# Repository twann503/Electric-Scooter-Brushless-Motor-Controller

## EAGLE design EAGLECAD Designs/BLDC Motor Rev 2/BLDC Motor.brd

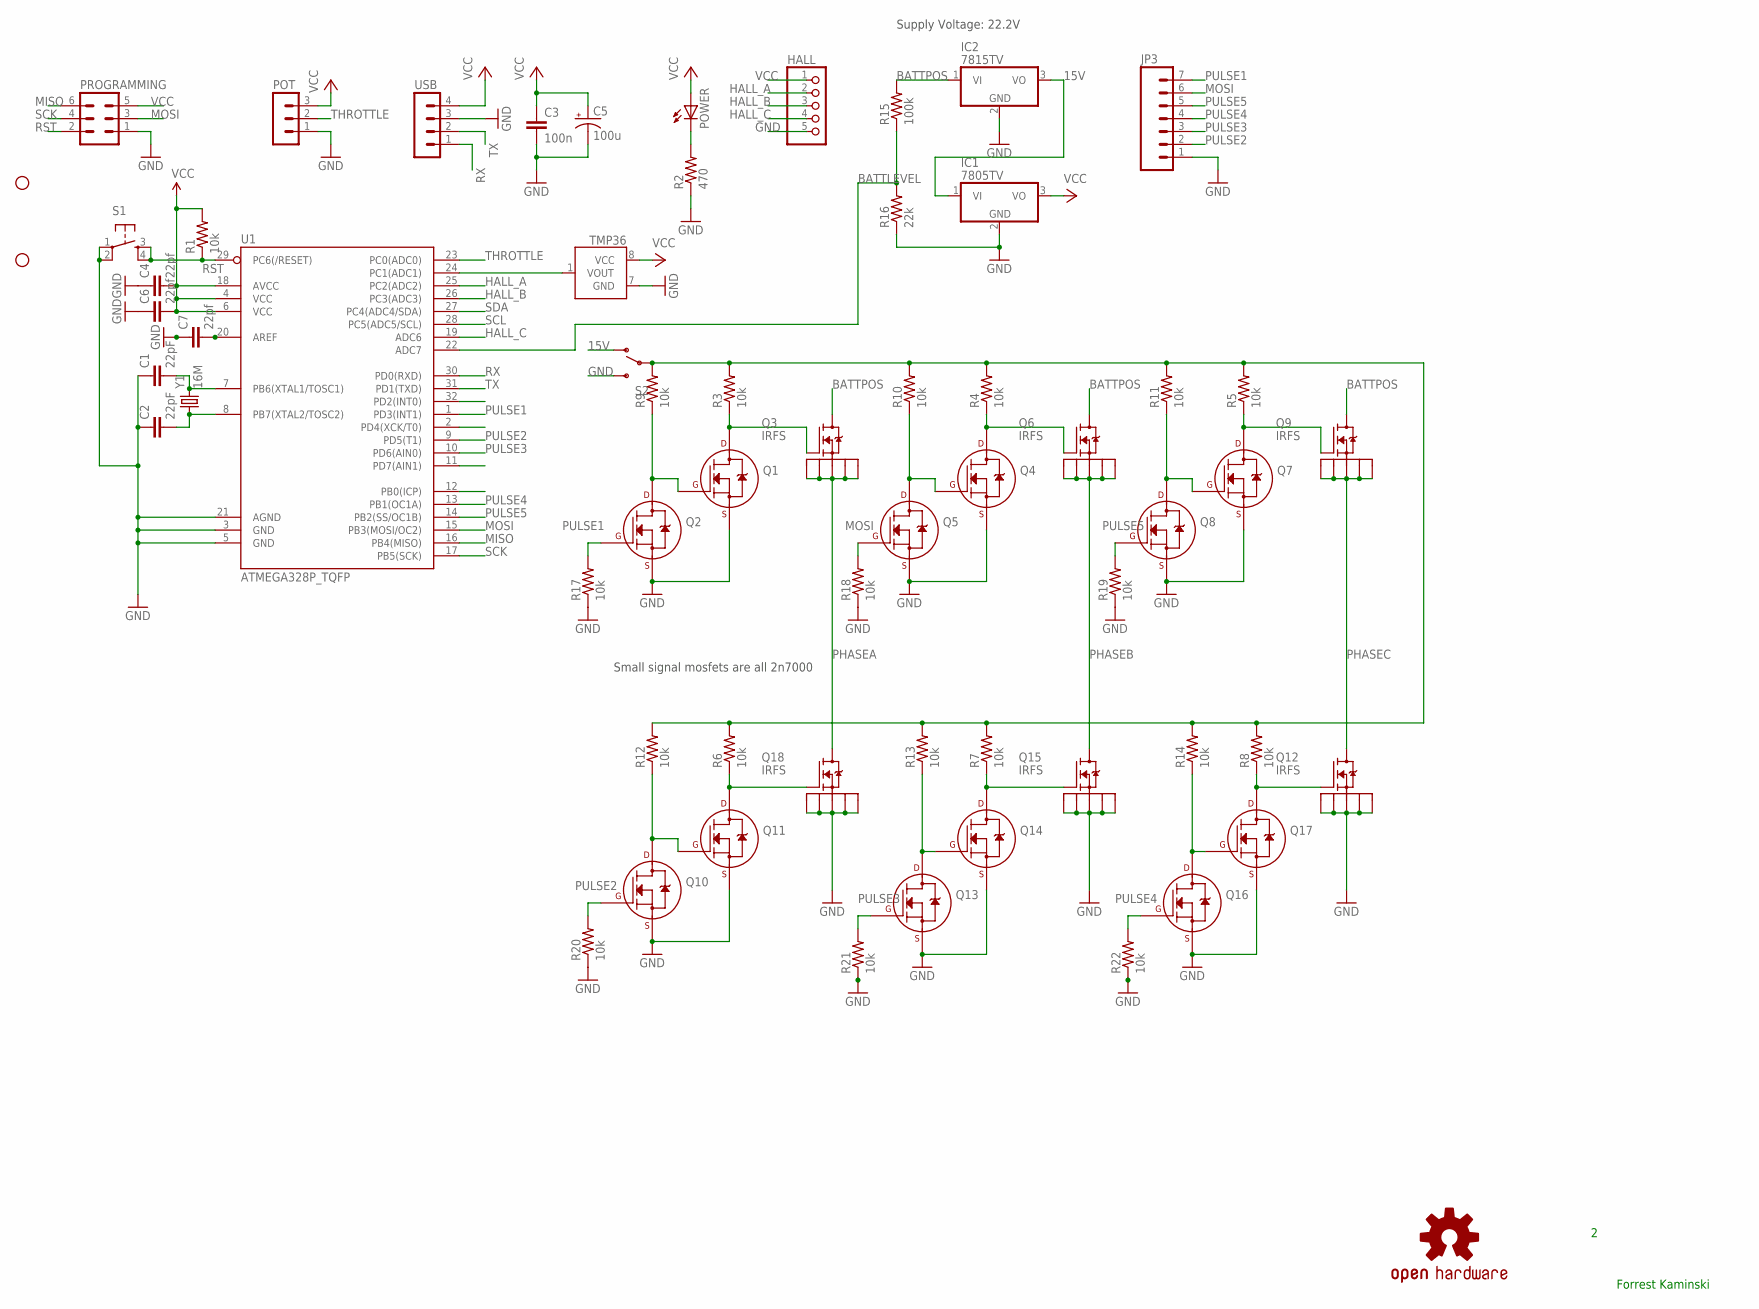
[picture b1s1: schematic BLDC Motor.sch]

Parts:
C1, C2: 22pF; 0805
C3: 100n; 0805
C4, C6, C7: 22pf; 0805
C5: 100u; CPOL-RADIAL-100UF-25V
HALL: PINHD-1X5; 1X05
IC1: 7805TV; TO220V
IC2: 7815TV; TO220V
JP1, JP2: STAND-OFF
JP3: M07; 1X07
POT: MA03-1
POWER: LEDSML0805; SML0805
PROGRAMMING: MA03-2
Q1, Q2, Q4, Q5, Q7, Q8, Q10, Q11, Q13, Q14, Q16, Q17: 2N7000_TO92; TO-92
Q3, Q6, Q9, Q12, Q15, Q18: IRFS; D2PAK-7
R1, R3, R4, R5, R6, R7, R8, R9, R10, R11, R12, R13, R14, R17, R18, R19, R20, R21, R22: 10k; 0805
R2: 470; 0805
R15: 100k; 0805
R16: 22k; 0805
S1: TAC_SWITCHPTH; TACTILE-PTH
S2: SWITCH-SPSTPTH_LOCK; SWITCH-SPDT_LOCK.007S
TMP36: TMP36SOIC; SOIC8
U1: ATMEGA328P_TQFP; TQFP32-08
U$1: OSHW-LOGOS; OSHW-LOGO-S
USB: MA04-1
Y1: 16M; HC49US

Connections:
15V: IC1.1 (VI), IC2.3 (VO), S2.1 (O)
BATTLEVEL: R15.1, R16.2, U1.22 (ADC7)
BATTPOS: IC2.1 (VI), Q3.D, Q6.D, Q9.D, R15.2
GND: C1.1, C2.1, C3.2, C4.1, C5.2 (-), C6.1, C7.1, HALL.5, IC1.2 (GND), IC2.2 (GND), JP3.1, POT.1, PROGRAMMING.1, Q1.1 (S), Q2.1 (S), Q4.1 (S), Q5.1 (S), Q7.1 (S), Q8.1 (S), Q10.1 (S), Q11.1 (S), Q12.S1, Q12.S2, Q12.S3, Q12.S4, Q12.S5, Q13.1 (S), Q14.1 (S), Q15.S1, Q15.S2, Q15.S3, Q15.S4, Q15.S5, Q16.1 (S), Q17.1 (S), Q18.S1, Q18.S2, Q18.S3, Q18.S4, Q18.S5, R2.1, R16.1, R17.1, R18.1, R19.1, R20.1, R21.1, R22.1, S1.1, S1.2, S2.3 (S), TMP36.7 (GND), U1.3 (GND), U1.5 (GND), U1.21 (AGND), USB.3
HALL_A: HALL.2, U1.25 (PC2(ADC2))
HALL_B: HALL.3, U1.26 (PC3(ADC3))
HALL_C: HALL.4, U1.19 (ADC6)
MISO: PROGRAMMING.6, U1.16 (PB4(MISO))
MOSI: JP3.6, PROGRAMMING.3, Q5.2 (G), R18.2, U1.15 (PB3(MOSI/OC2))
unnamed: C2.2, U1.8 (PB7(XTAL2/TOSC2)), Y1.1
unnamed: C1.2, U1.7 (PB6(XTAL1/TOSC1)), Y1.2
unnamed: POWER.C, R2.2
unnamed: Q10.3 (D), Q11.2 (G), R12.1
unnamed: Q1.3 (D), Q3.G, R3.1
unnamed: TMP36.1 (VOUT), U1.24 (PC1(ADC1))
unnamed: C7.2, U1.20 (AREF)
unnamed: Q1.2 (G), Q2.3 (D), R9.1
unnamed: Q4.3 (D), Q6.G, R4.1
unnamed: Q4.2 (G), Q5.3 (D), R10.1
unnamed: R3.2, R4.2, R5.2, R6.2, R7.2, R8.2, R9.2, R10.2, R11.2, R12.2, R13.2, R14.2, S2.2
unnamed: Q7.3 (D), Q9.G, R5.1
unnamed: Q7.2 (G), Q8.3 (D), R11.1
unnamed: Q11.3 (D), Q18.G, R6.1
unnamed: Q13.3 (D), Q14.2 (G), R13.1
unnamed: Q12.G, Q17.3 (D), R8.1
unnamed: Q16.3 (D), Q17.2 (G), R14.1
unnamed: Q14.3 (D), Q15.G, R7.1
PHASEA: Q3.S1, Q3.S2, Q3.S3, Q3.S4, Q3.S5, Q18.D
PHASEB: Q6.S1, Q6.S2, Q6.S3, Q6.S4, Q6.S5, Q15.D
PHASEC: Q9.S1, Q9.S2, Q9.S3, Q9.S4, Q9.S5, Q12.D
PULSE1: JP3.7, Q2.2 (G), R17.2, U1.1 (PD3(INT1))
PULSE2: JP3.2, Q10.2 (G), R20.2, U1.9 (PD5(T1))
PULSE3: JP3.3, Q13.2 (G), R21.2, U1.10 (PD6(AIN0))
PULSE4: JP3.4, Q16.2 (G), R22.2, U1.13 (PB1(OC1A))
PULSE5: JP3.5, Q8.2 (G), R19.2, U1.14 (PB2(SS/OC1B))
RST: PROGRAMMING.2, R1.1, S1.3, S1.4, U1.29 (PC6(/RESET))
RX: U1.30 (PD0(RXD)), USB.1
SCK: PROGRAMMING.4, U1.17 (PB5(SCK))
SCL: U1.28 (PC5(ADC5/SCL))
SDA: U1.27 (PC4(ADC4/SDA))
THROTTLE: POT.2, U1.23 (PC0(ADC0))
TX: U1.31 (PD1(TXD)), USB.2
VCC: C3.1, C4.2, C5.1 (+), C6.2, HALL.1, IC1.3 (VO), POT.3, POWER.A, PROGRAMMING.5, R1.2, TMP36.8 (VCC), U1.4 (VCC), U1.6 (VCC), U1.18 (AVCC), USB.4

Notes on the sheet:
Supply Voltage: 22.2V
Forrest Kaminski
Small signal mosfets are all 2n7000

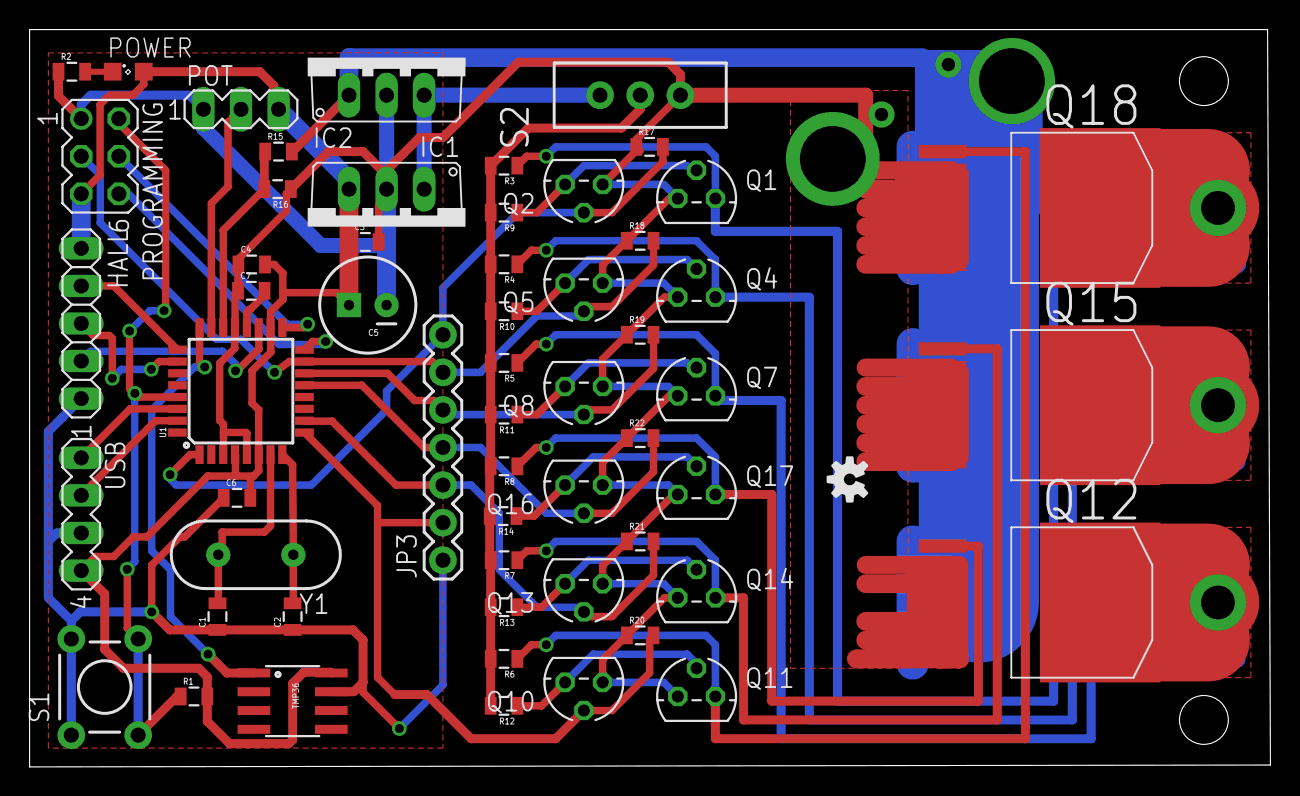
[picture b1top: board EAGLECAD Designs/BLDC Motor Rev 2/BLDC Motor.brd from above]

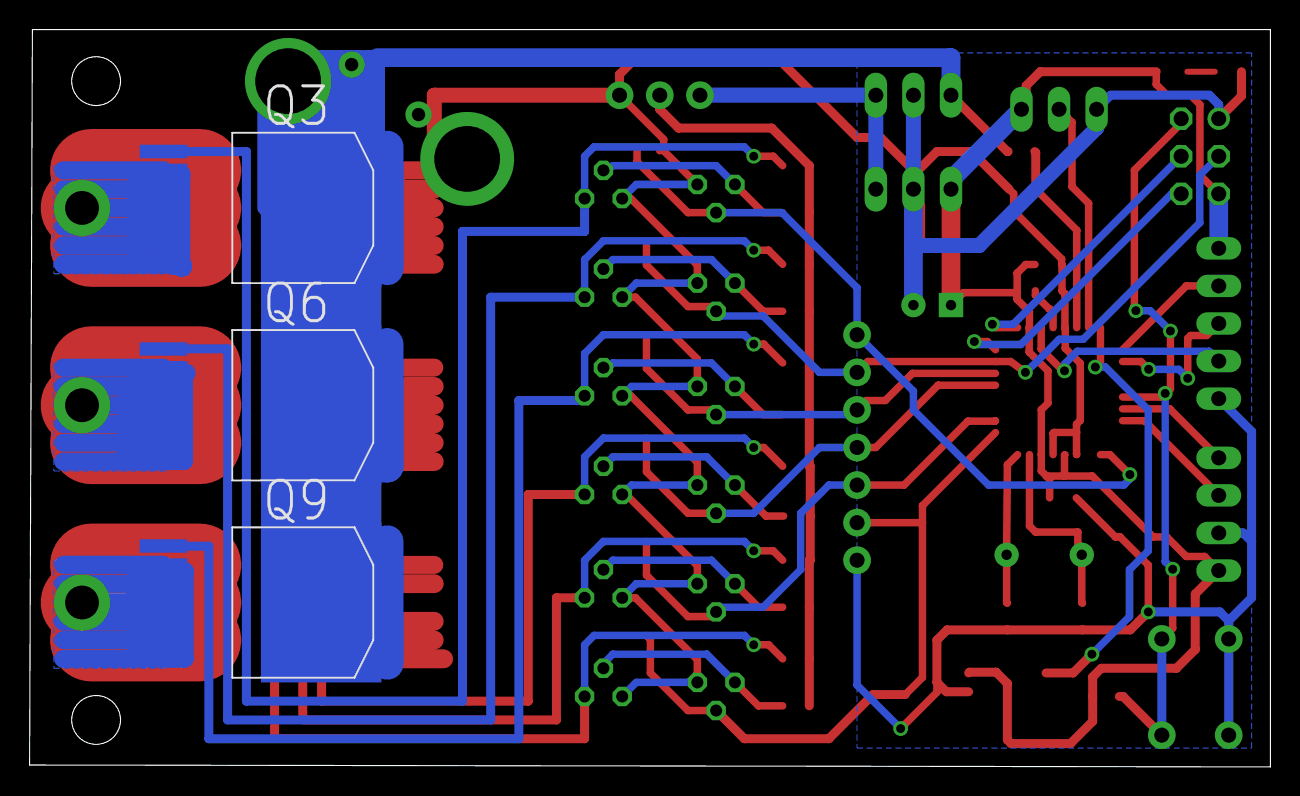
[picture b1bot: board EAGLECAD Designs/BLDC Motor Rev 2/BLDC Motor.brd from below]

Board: 2 copper layers, 83.9 x 49.8 mm, 63 parts (3 on the bottom side), 41 nets.

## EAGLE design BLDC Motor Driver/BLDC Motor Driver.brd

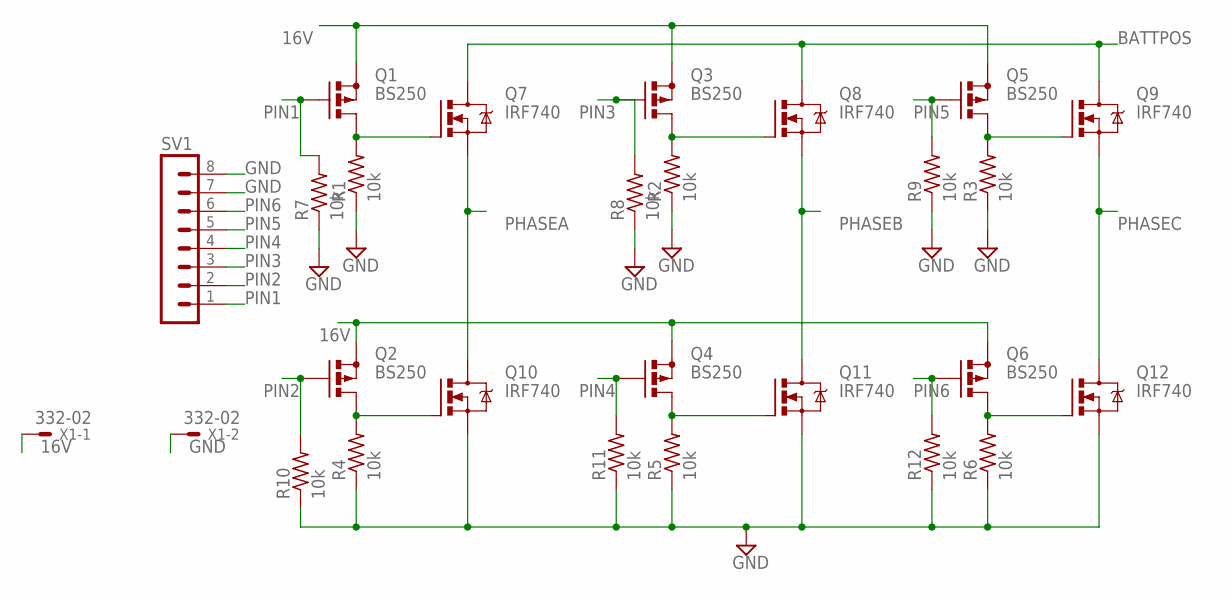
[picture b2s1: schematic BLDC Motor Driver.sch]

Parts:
Q1, Q2, Q3, Q4, Q5, Q6: BS250; SOT54E
Q7, Q8, Q9, Q10, Q11, Q12: IRF740; TO220BV
R1, R2, R3, R4, R5, R6, R7, R8, R9, R10, R11, R12: 10k; R0805
SV1: MA08-1
X1: 332-02

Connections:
16V: Q1.S, Q2.S, Q3.S, Q4.S, Q5.S, Q6.S, X1.1; also elsewhere on the board
BATTPOS: Q7.D, Q8.D, Q9.D
GND: Q10.S, Q11.S, Q12.S, R1.1, R2.1, R3.1, R4.1, R5.1, R6.1, R7.1, R8.1, R9.1, R10.1, R11.1, R12.1, SV1.7, SV1.8, X1.2; also elsewhere on the board
unnamed: Q1.D, Q7.G, R1.2
unnamed: Q3.D, Q8.G, R2.2
unnamed: Q5.D, Q9.G, R3.2
unnamed: Q2.D, Q10.G, R4.2
unnamed: Q4.D, Q11.G, R5.2
unnamed: Q6.D, Q12.G, R6.2
PHASEA: Q7.S, Q10.D
PHASEB: Q8.S, Q11.D
PHASEC: Q9.S, Q12.D
PIN1: Q1.G, R7.2, SV1.1
PIN2: Q2.G, R10.2, SV1.2
PIN3: Q3.G, R8.2, SV1.3
PIN4: Q4.G, R11.2, SV1.4
PIN5: Q5.G, R9.2, SV1.5
PIN6: Q6.G, R12.2, SV1.6

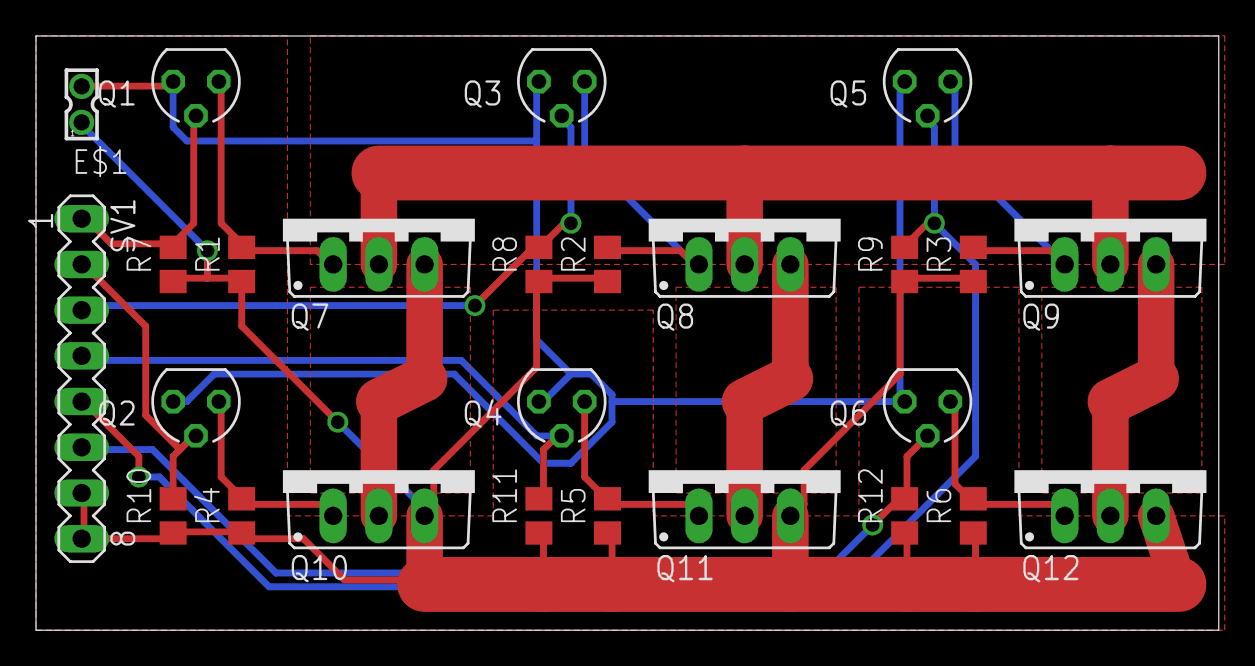
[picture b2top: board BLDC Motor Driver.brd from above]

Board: 2 copper layers, 65.7 x 33.0 mm, 26 parts (0 on the bottom side), 18 nets.

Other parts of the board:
E$1: 332-02

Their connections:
16V: E$1.2; also elsewhere on the board
GND: E$1.1; also elsewhere on the board

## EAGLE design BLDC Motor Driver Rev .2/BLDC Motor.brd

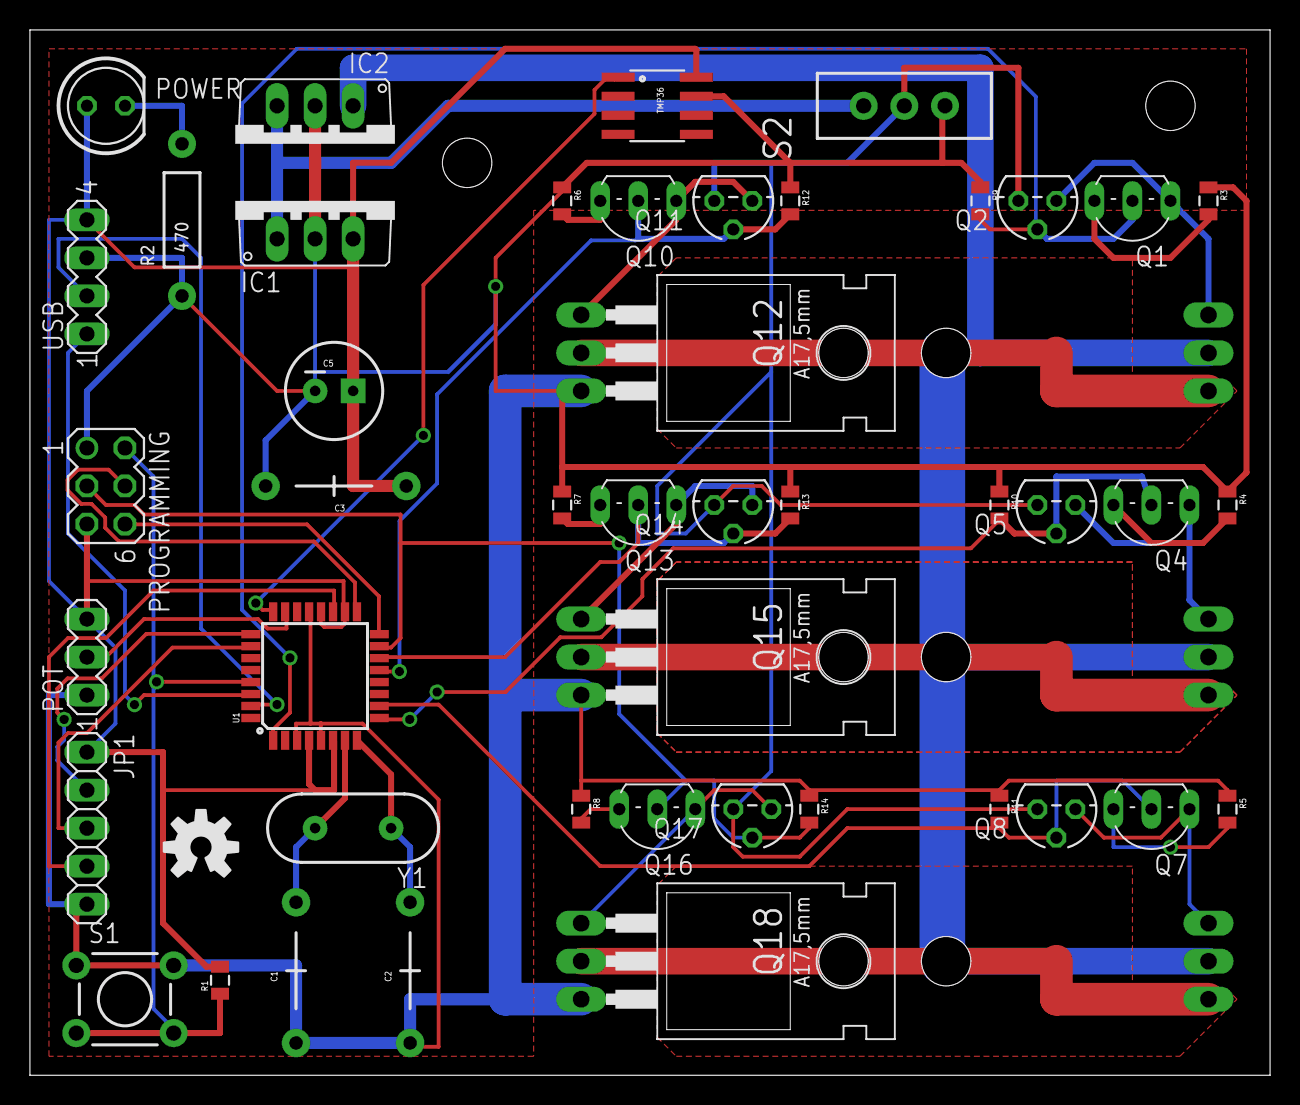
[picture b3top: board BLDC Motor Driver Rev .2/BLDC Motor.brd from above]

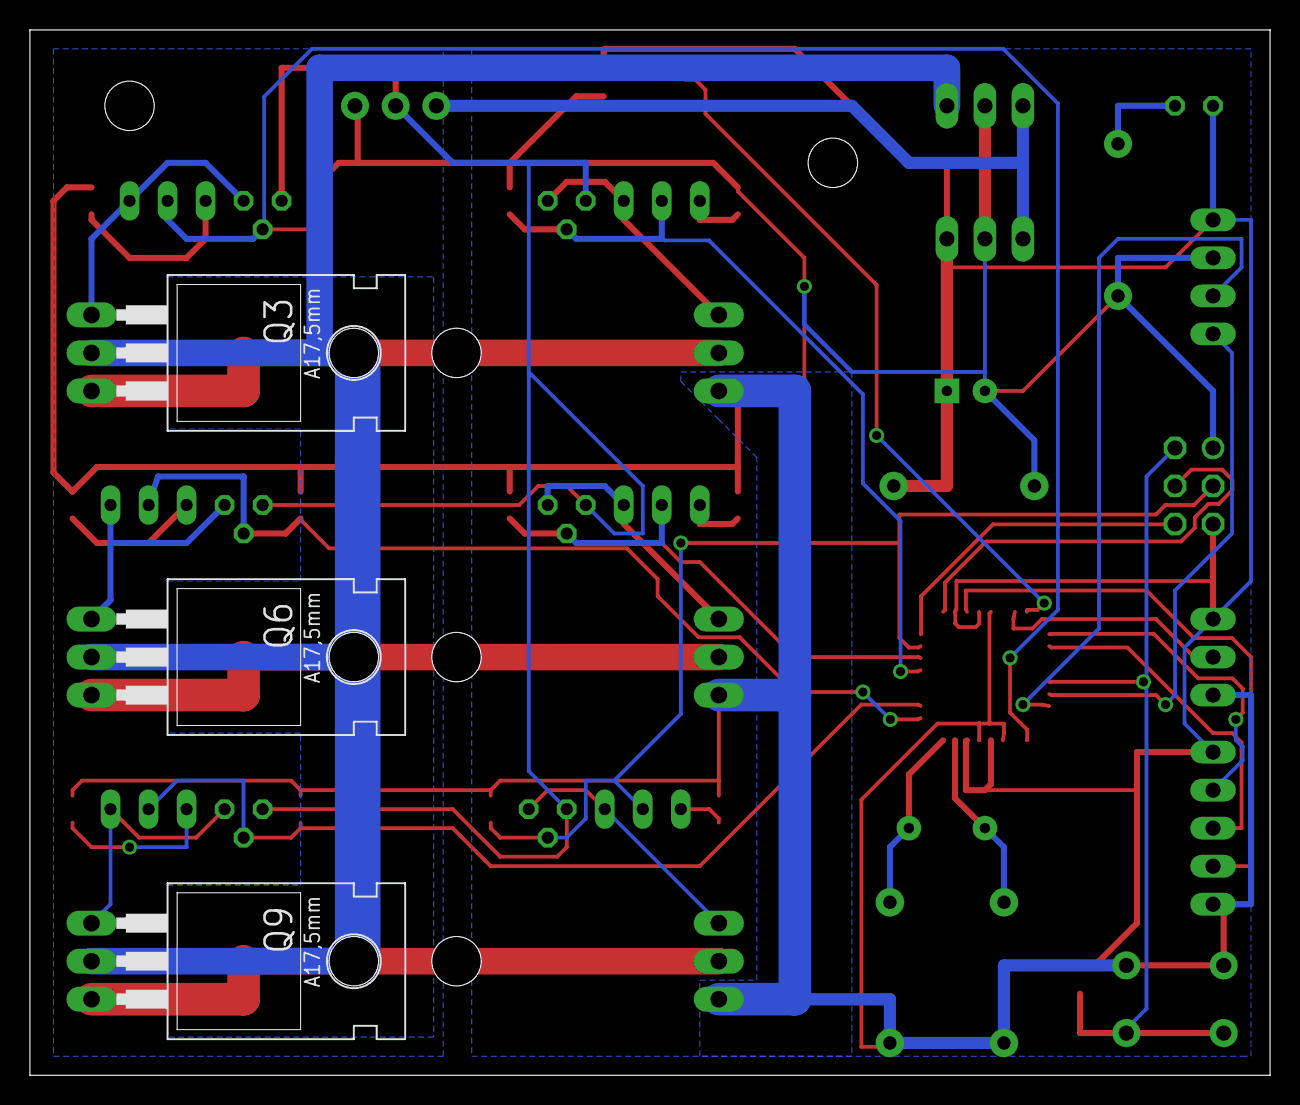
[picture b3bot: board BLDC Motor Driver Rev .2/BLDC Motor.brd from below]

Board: 2 copper layers, 82.9 x 69.8 mm, 51 parts (3 on the bottom side), 39 nets.

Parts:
C1, C2: 22pF; CAP-PTH-LARGE
C3: 0.1u; CAP-PTH-LARGE
C5: 100u; CPOL-RADIAL-100UF-25V
IC1: 7805TV; TO220V
IC2: 7815TV; TO220V
JP1: 1X05
JP2, JP4: STAND-OFF
POT: MA03-1
POWER: LED5MM
PROGRAMMING: MA03-2
Q1, Q4, Q7, Q10, Q13, Q16: TP2104; TO92-OVAL
Q2, Q5, Q8, Q11, Q14, Q17: TO-92
Q3, Q6, Q9, Q12, Q15, Q18: IRFB4115; TO220
R1, R3, R4, R5, R6, R7, R8, R9, R10, R11, R12, R13, R14: 10k; 0805
R2: 470; AXIAL-0.4
S1: TACTILE-PTH
S2: SWITCH-SPDT_LOCK.007S
TMP36: SOIC8
U1: ATMEGA328P_TQFP; TQFP32-08
U$1: OSHW-LOGOM; OSHW-LOGO-M
USB: MA04-1
Y1: 16M; HC49US

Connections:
15V: IC1.1, IC2.3, S2.1
BATTPOS: IC2.1, Q3.2, Q6.2, Q9.2
GND: C1.1, C2.1, C3.2, C5.2, IC1.2, IC2.2, JP1.5, POT.1, PROGRAMMING.1, Q12.3, Q15.3, Q18.3, R2.P$1, R3.1, R4.1, R5.1, R6.1, R7.1, R8.1, R9.1, R10.1, R11.1, R12.1, R13.1, R14.1, S1.1, S1.2, S2.3, TMP36.7, U1.3, U1.5, U1.21, USB.3
HALL_A: JP1.2, U1.25
HALL_B: JP1.3, U1.26
HALL_C: JP1.4, U1.19
MISO: PROGRAMMING.6, U1.16
MOSI: PROGRAMMING.3, Q16.2, Q17.2, R14.2, U1.15
unnamed: C2.2, U1.8, Y1.1
unnamed: C1.2, U1.7, Y1.2
unnamed: POWER.K, R2.P$2
unnamed: Q1.3, R3.2
unnamed: Q1.1, Q2.1, Q3.1
unnamed: TMP36.1, U1.24
unnamed: Q2.3, Q5.3, Q8.3, Q11.3, Q14.3, Q17.3, S2.2
unnamed: Q4.3, R4.2
unnamed: Q4.1, Q5.1, Q6.1
unnamed: Q7.3, R5.2
unnamed: Q7.1, Q8.1, Q9.1
unnamed: Q10.3, R6.2
unnamed: Q10.1, Q11.1, Q12.1
unnamed: Q13.3, R7.2
unnamed: Q13.1, Q14.1, Q15.1
unnamed: Q16.3, R8.2
unnamed: Q16.1, Q17.1, Q18.1
PHASEA: Q3.3, Q12.2
PHASEB: Q6.3, Q15.2
PHASEC: Q9.3, Q18.2
PULSE1: Q1.2, Q2.2, R9.2, U1.1
PULSE2: Q4.2, Q5.2, R10.2, U1.9
PULSE3: Q7.2, Q8.2, R11.2, U1.10
PULSE4: Q10.2, Q11.2, R12.2, U1.13
PULSE5: Q13.2, Q14.2, R13.2, U1.14
RST: PROGRAMMING.2, R1.1, S1.3, S1.4, U1.29
RX: U1.30, USB.1
SCK: PROGRAMMING.4, U1.17
THROTTLE: POT.2, U1.23
TX: U1.31, USB.2
VCC: C3.1, C5.1, IC1.3, JP1.1, POT.3, POWER.A, PROGRAMMING.5, R1.2, TMP36.8, U1.4, U1.6, U1.18, U1.20, USB.4

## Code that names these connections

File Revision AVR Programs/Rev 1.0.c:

#define F_CPU 16000000UL         //Says to the compiler which is our clock frequency, permits the delay functions to be very accurate
#include <avr/io.h>              //General definitions of the registers values
#include <util/delay.h>          //This is where the delay functions are located
#include <avr/interrupt.h>

#define FOSC 16000000            // Clock Speed
#define BAUD 9600
#define MYUBRR FOSC/16/BAUD -1
#define OFF 255;

volatile int counts = 0;
volatile int counts2 = 0;

volatile uint8_t ADCvalue;
volatile long Speed = 255;
uint8_t  states = 7;
volatile int duration = 0;

#define pin7 OCR0B
#define pin6 OCR0A
#define pin5 OCR1A
#define pin4 OCR1B
#define pin3 OCR2A
#define pin2 OCR2B
#define Freq 300



void turnOff() {
	OCR0B = OFF; //PD5, pin 7
	OCR0A = OFF; //PD6, pin 6
	OCR1A = OFF; //PB1, pin 5
	OCR1B = OFF; //PB2, pin 4
	OCR2A = OFF; //PB3, pin 3
	OCR2B = OFF; //PD3, pin 2
}

long mapp(uint8_t x, long in_min, long in_max, long out_min, long out_max) {
	return (x - in_min) * (out_max - out_min) / (in_max - in_min) + out_min;
}


ISR(TIMER1_OVF_vect)
{
	counts++;
	if ( counts > Freq) { //control freq.
		
		//this controls ON time
		if(duration == 0) {
			Speed = OFF;
		}
		else {
			Speed = 1;
		}
		counts = 0;
		counts2 = 0;
	}
	if ( counts2 >= duration) {
		Speed = OFF;
	}
	++ counts2;
}



int main(void)
{
	
	int isReady = 1;

	//SET pin 2-7 as OUTPUT
	DDRB |= (1 << DDB1) | (1 << DDB2) | (1 << DDB3);    // sets port 3,4,5 as
	DDRD |= (1 << DDD3) | (1 << DDD5) | (1 << DDD6);    // pins 2,6,7 as output
	
	//TIMER0
	TCCR0A |= (1 << COM0A1) | (1 << COM0A0)| (1 << COM0B1) | (1 << COM0B0);	// set inverting mode
	TCCR0A |= (1 << WGM01) | (1 << WGM00);		// set fast PWM Mode
	TCCR0B |= (1 << CS00);				// set pre-scaler to 8 and starts PWM
	
	//TIMER1
	TCCR1A |= (1 << COM1A1) | (1 << COM1B1) | (1 << COM1A0) | (1 << COM1B0);	// set non-inverting mode
	TCCR1A |= (1 << WGM10);		// set fast PWM mode 8 bit
	TCCR1B |= (1 << WGM12);		// set fast PWM mode 8 bit
	TCCR1B |= (1 << CS10);		// START the timer with no pre-scaler
	
	//SET UP FOR TIMER2 PWM PINS
	TCCR2A |= (1 << COM2A1) | (1 << COM2B1) | (1 << COM2A0) | (1 << COM2B0) ;	// set non - inverting mode for both lines
	TCCR2A |= (1 << WGM21) | (1 << WGM20);		// set fast PWM Mode
	TCCR2B |= (1 << CS20);				// sets pre-scaler to 8 and starts PWM
	
	//SET UP FOR HALL EFFECT PINS
	DDRC &= ~(1 << DDC2) | ~(1 << DDC3) | ~(1 << DDC0); //sets PC2 & PC3 & PC0 as inputs for HALL_A, HALL_B, HALL_C
	PORTC |= (1 << PORTC2) | (1 << PORTC3) | (1 << PORTC0); //enable pull up resistor on PC2 & PC3 & PC0 for HALL_A, HALL_B, HALL_C
	
	ADMUX = 6;               			 // use ADC6
	ADMUX |= (1 << REFS0);    			 // use AVcc as the reference
	ADMUX |= (1 << ADLAR);   			 // Right adjust for 8 bit resolution
	ADCSRA |=  (1 << ADPS1) | (1 << ADPS0); 	 // 128 prescale for 16Mhz
	ADCSRA |= (1 << ADATE);  		         // Set ADC Auto Trigger Enable
	ADCSRB = 0;              			 // 0 for free running mode
	ADCSRA |= (1 << ADEN); 				 // Enable the ADC
	ADCSRA |= (1 << ADSC);   			 // Start the ADC conversion

	turnOff();

	TIMSK1 = (1 << TOIE1);
	sei();
	
	while (1) {
		
		////gets state of hall sensors
		states = (PINC & (1 << PC2)) + (((PINC & (1 << PC3))) >> 2 ) + (PINC & (1 << PC0));
		
		ADCvalue = ADCH;
		duration = mapp(ADCvalue, 70, 215, 0, Freq - 1);
		
		if (duration > Freq - 1)
			duration = Freq - 1;
		else if (duration < 1)
			duration = 0;
		
		if (isReady > 0) {
			
			switch (states) {
				
				case 1 :
				pin5 = OFF;     //BN
				pin2 = OFF;     //YP
				pin7 = OFF;     //YN
				pin3 = OFF;     //RP
				pin6 = Speed;   //RN
				pin4 = Speed;   //BP
				break;
				
				case 2 :
				pin6 = OFF;   //RN
				pin7 = OFF;   //YN
				pin4 = OFF;   //BP
				pin3 = OFF;   //RP
				pin5 = Speed; //BN
				pin2 = Speed; //YP
				break;
				
				case 3 :
				pin7 = OFF;   //YN
				pin4 = OFF;   //BP
				pin3 = OFF;   //RP
				pin5 = OFF;   //BN
				pin6 = Speed; //RN
				pin2 = Speed; //YP
				break;
				
				case 4 :
				pin6 = OFF;   //YN
				pin4 = OFF;   //BP
				pin2 = OFF;   //RP
				pin5 = OFF;   //BN
				pin7 = Speed; //RN
				pin3 = Speed; //YP
				break;
				
				case 5 :
				pin6 = OFF;   //RN
				pin7 = OFF;   //YN
				pin4 = OFF;   //BP
				pin3 = OFF;   //RP
				pin7 = Speed; //BN
				pin4 = Speed; //YP
				break;
				
				case 6 :
				pin6 = OFF;   //RN
				pin7 = OFF;   //YN
				pin4 = OFF;   //BP
				pin2 = OFF;   //YP
				pin5 = Speed; //BN
				pin3 = Speed; //RP
				break;
				
				default:
				turnOff();
				break;
			}
		}
	}
}

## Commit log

2016-10-11 Added original idea comparison
2016-10-11 Added design reference documents for more info
2016-10-11 Adding a schedule text file
2016-10-11 Added Eagle Files
2016-10-13 Added Project Proposal
2016-10-28 Adding rev .2 to board files
2016-11-01 Changing the Rev 2 board up
2016-11-01 removed old rev 2 folder
2016-11-02 Added personal weekly log
2016-11-02 added weekly log
2016-11-03 Updated BLDC schematic
2016-11-08 Updating board
2016-11-08 added gantt chart
2016-11-10 Adding capacitors to the processor for better stability
2016-11-15 Updated Gate driver on board, moved weekly reports to folder
2016-11-17 homework 5 added
2016-11-17 Final board design, added test arduino code
2016-11-23 Changing arduino code
2016-11-24 Added test plan document
2016-11-24 Added Homework 6, test plan
2016-11-24 Moved test plan to folder
2016-12-06 Reorganized our directory
2016-12-06 Rename Working Spinner.c to Rev 0.8.c
2016-12-06 64k PWM
2016-12-06 1st functional code for speed controller
2016-12-06 Rev 0.3 update
2016-12-06 1st Working code
2016-12-06 Rev 0.2 updated some code
2016-12-06 Almost Final code
2016-12-06 Final working code
    Added 300Hz PWM ontop of 64KHz PWM wave to control speed
2016-12-06 Added microsoft project file for scheduling
2016-12-06 Organized everything
2016-12-06 Reorganized everything
2016-12-07 Reuploaded Main Document
2016-12-07 Added files from gdrive
2016-12-08 added weekly reports

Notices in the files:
parts and their libraries:
SparkFun: Licensing: CC v3.0 Share-Alike You are welcome to use this library for commercial purposes.
SparkFun-DigitalIC: Licensing: Creative Commons ShareAlike 4.0 International - https://creativecommons.org/licenses/by-sa/4.0
